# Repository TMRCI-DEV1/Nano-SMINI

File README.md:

# Nano-SMINI
Arduino Nano-based CMRI SMINI

Shield: [![CC BY-SA 4.0][cc-by-sa-shield]][cc-by-sa]

This work is licensed under a
[Creative Commons Attribution-ShareAlike 4.0 International License][cc-by-sa].

[![CC BY-SA 4.0][cc-by-sa-image]][cc-by-sa]

[cc-by-sa]: http://creativecommons.org/licenses/by-sa/4.0/
[cc-by-sa-image]: https://licensebuttons.net/l/by-sa/4.0/88x31.png
[cc-by-sa-shield]: https://img.shields.io/badge/License-CC%20BY--SA%204.0-lightgrey.svg

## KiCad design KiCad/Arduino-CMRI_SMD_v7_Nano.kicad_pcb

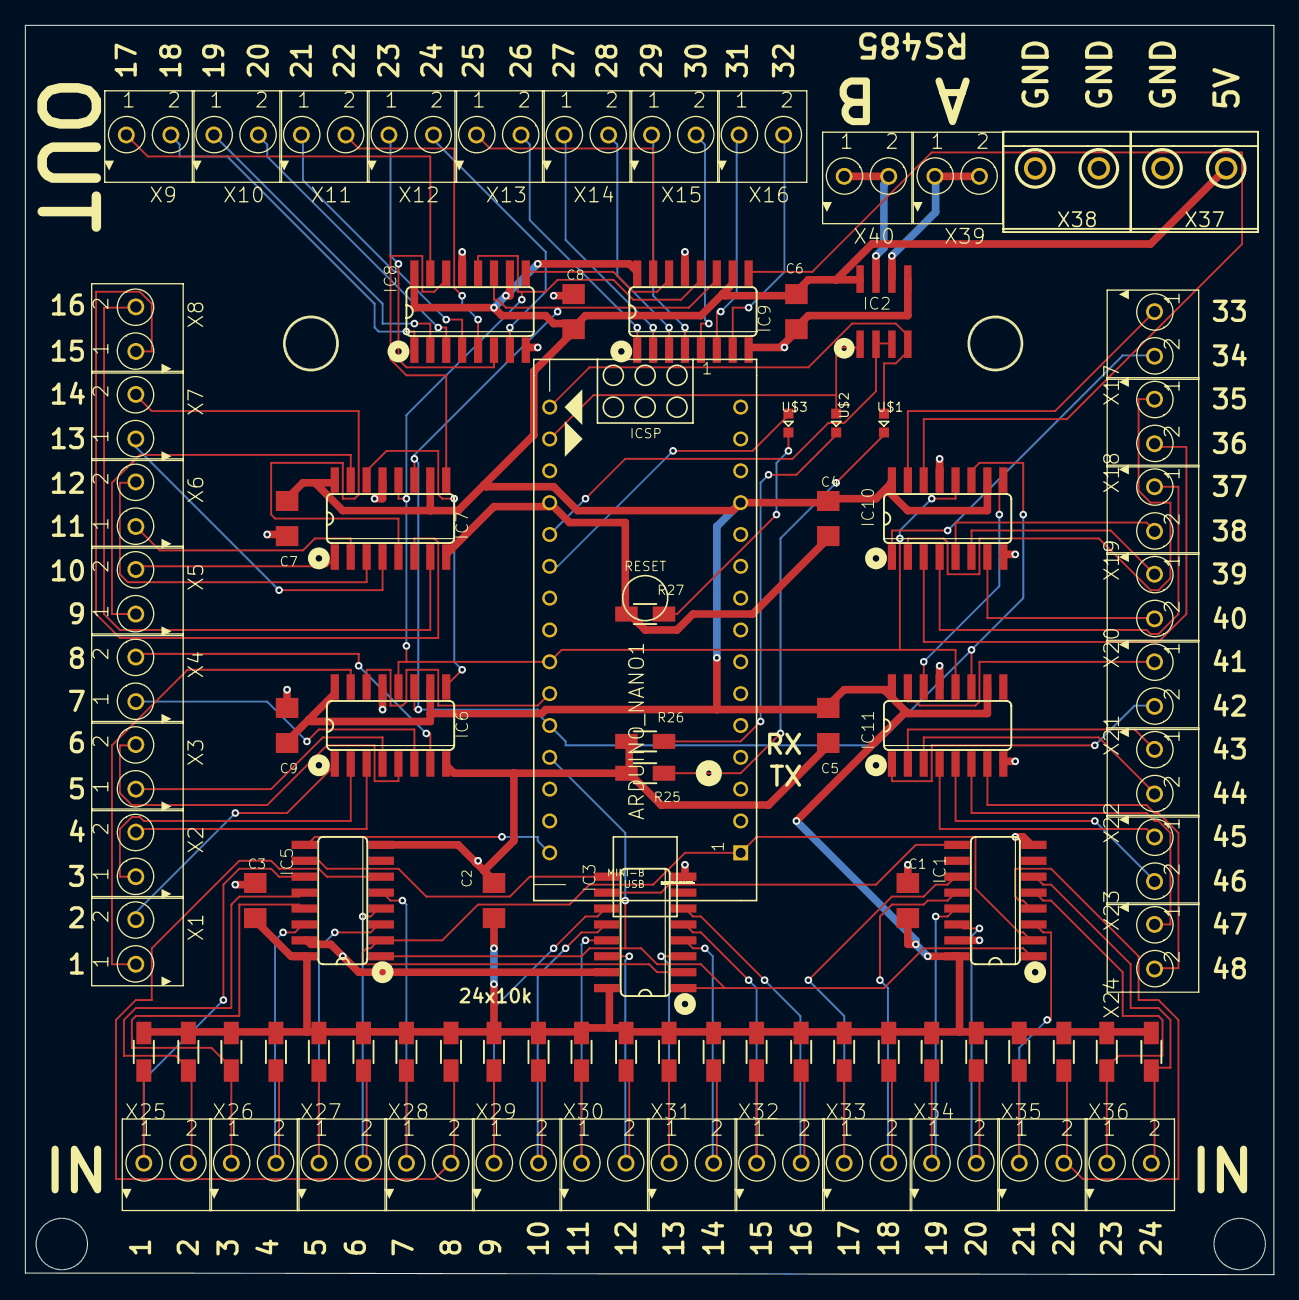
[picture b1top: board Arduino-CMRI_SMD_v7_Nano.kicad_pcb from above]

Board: 2 copper layers, 99.6 x 99.7 mm, 92 parts (0 on the bottom side), 96 nets.

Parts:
ARDUINO_NANO1: ARDUINO_NANO
C1, C2, C3, C4, C5, C6, C7, C8, C9: 100nF; 1206
H1, H2: MOUNT-HOLE4.1; 4,1
IC1, IC3, IC5: 74HC165D; SO16
IC2: MAX485; SO08
IC6, IC7, IC8, IC9, IC10, IC11: 74HC595D; SO16
R1, R2, R3, R4, R5, R6, R7, R8, R9, R10, R11, R12, R13, R14, R15, R16, R17, R18, R19, R20, R21, R22, R23, R24: 10k; R1206W
R25, R26, R27: 1k; R1206W
U$1: TX; CHIPLED_0603
U$2: RX; CHIPLED_0603
U$3: status; CHIPLED_0603
X1, X2, X3, X4, X5, X6, X7, X8, X9, X10, X11, X12, X13, X14, X15, X16, X17, X18, X19, X20, X21, X22, X23, X24, X25, X26, X27, X28, X29, X30, X31, X32, X33, X34, X35, X36, X39, X40: TERMINAL_2P_3,5MM_V2; TERMINAL_2P_3,5MM
X37, X38: W237-132

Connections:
A: IC2.6, X39.P$1, X39.P$2
B: IC2.7, X40.P$1, X40.P$2
D2: ARDUINO_NANO1.20, IC2.2, IC2.3
D3: ARDUINO_NANO1.21, U$3.A
D6: ARDUINO_NANO1.24, IC6.12, IC7.12, IC8.12, IC9.12, IC10.12, IC11.12
D7: ARDUINO_NANO1.25, IC6.14
D8: ARDUINO_NANO1.26, IC6.11, IC7.11, IC8.11, IC9.11, IC10.11, IC11.11
D9: ARDUINO_NANO1.27, IC1.1, IC3.1, IC5.1
D12: ARDUINO_NANO1.30, IC5.9
D13: ARDUINO_NANO1.1, IC1.2, IC3.2, IC5.2
GND: ARDUINO_NANO1.14, ARDUINO_NANO1.19, C1.1, C2.1, C3.1, C4.1, C5.1, C6.1, C7.1, C8.1, C9.1, IC1.8, IC1.15, IC2.5, IC3.8, IC3.15, IC5.8, IC5.15, IC6.8, IC6.13, IC7.8, IC7.13, IC8.8, IC8.13, IC9.8, IC9.13, IC10.8, IC10.13, IC11.8, IC11.13, R25.1, R26.1, R27.1, X37.2, X38.1, X38.2
unnamed: IC5.11, R24.1, X25.P$1
unnamed: IC1.9, IC3.10
unnamed: IC5.12, R23.1, X25.P$2
unnamed: IC3.9, IC5.10
unnamed: IC5.13, R22.1, X26.P$1
unnamed: IC6.9, IC7.14
unnamed: IC5.14, R21.1, X26.P$2
unnamed: IC9.9, IC10.14
unnamed: IC5.3, R20.1, X27.P$1
unnamed: IC7.9, IC8.14
unnamed: IC5.4, R19.1, X27.P$2
unnamed: IC10.9, IC11.14
unnamed: IC5.5, R18.1, X28.P$1
unnamed: IC6.15, X1.P$1
unnamed: IC5.6, R17.1, X28.P$2
unnamed: IC6.1, X1.P$2
unnamed: R25.2, U$1.C
unnamed: IC6.2, X2.P$1
unnamed: IC3.11, R16.1, X29.P$1
unnamed: IC6.3, X2.P$2
unnamed: IC3.12, R15.1, X29.P$2
unnamed: IC6.4, X3.P$1
unnamed: IC3.13, R14.1, X30.P$1
unnamed: IC6.5, X3.P$2
unnamed: IC3.14, R13.1, X30.P$2
unnamed: IC6.6, X4.P$1
unnamed: IC3.3, R12.1, X31.P$1
unnamed: IC6.7, X4.P$2
unnamed: IC3.4, R11.1, X31.P$2
unnamed: IC7.15, X5.P$1
unnamed: IC3.5, R10.1, X32.P$1
unnamed: IC7.1, X5.P$2
unnamed: IC3.6, R9.1, X32.P$2
unnamed: IC7.2, X6.P$1
unnamed: IC1.11, R8.1, X33.P$1
unnamed: IC7.3, X6.P$2
unnamed: IC1.12, R7.1, X33.P$2
unnamed: IC7.4, X7.P$1
unnamed: IC1.13, R6.1, X34.P$1
unnamed: IC7.5, X7.P$2
unnamed: IC1.14, R5.1, X34.P$2
unnamed: IC7.6, X8.P$1
unnamed: IC1.3, R4.1, X35.P$1
unnamed: IC7.7, X8.P$2
unnamed: IC1.4, R3.1, X35.P$2
unnamed: IC8.15, X9.P$1
unnamed: IC1.5, R2.1, X36.P$1
unnamed: IC8.1, X9.P$2
unnamed: IC8.2, X10.P$1
unnamed: IC8.3, X10.P$2
unnamed: IC8.9, IC9.14
unnamed: IC8.4, X11.P$1
unnamed: IC8.5, X11.P$2
unnamed: R26.2, U$2.C
unnamed: IC1.6, R1.1, X36.P$2
unnamed: R27.2, U$3.C
unnamed: IC8.6, X12.P$1
unnamed: IC8.7, X12.P$2
unnamed: IC9.15, X13.P$1
unnamed: IC9.1, X13.P$2
unnamed: IC9.2, X14.P$1
unnamed: IC9.3, X14.P$2
unnamed: IC9.4, X15.P$1
unnamed: IC9.5, X15.P$2
unnamed: IC9.6, X16.P$1
unnamed: IC9.7, X16.P$2
unnamed: IC10.15, X17.P$1
unnamed: IC10.1, X17.P$2
unnamed: IC10.2, X18.P$1
unnamed: IC10.3, X18.P$2
unnamed: IC10.4, X19.P$1
unnamed: IC10.5, X19.P$2
unnamed: IC10.6, X20.P$1
unnamed: IC10.7, X20.P$2
unnamed: IC11.15, X21.P$1
unnamed: IC11.1, X21.P$2
unnamed: IC11.2, X22.P$1
unnamed: IC11.3, X22.P$2
unnamed: IC11.4, X23.P$1
unnamed: IC11.5, X23.P$2
unnamed: IC11.6, X24.P$1
unnamed: IC11.7, X24.P$2
RX: ARDUINO_NANO1.17, IC2.1, U$2.A
TX: ARDUINO_NANO1.16, IC2.4, U$1.A
VCC: ARDUINO_NANO1.12, C1.2, C2.2, C3.2, C4.2, C5.2, C6.2, C7.2, C8.2, C9.2, IC1.16, IC2.8, IC3.16, IC5.16, IC6.10, IC6.16, IC7.10, IC7.16, IC8.10, IC8.16, IC9.10, IC9.16, IC10.10, IC10.16, IC11.10, IC11.16, R1.2, R2.2, R3.2, R4.2, R5.2, R6.2, R7.2, R8.2, R9.2, R10.2, R11.2, R12.2, R13.2, R14.2, R15.2, R16.2, R17.2, R18.2, R19.2, R20.2, R21.2, R22.2, R23.2, R24.2, X37.1

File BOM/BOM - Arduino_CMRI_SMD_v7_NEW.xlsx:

Designators | Value | Footprint | Manufacturer Part Number | Quantity
C1, C2, C3, C4, C5, C6, C7, C8, C9 | 100nF | 1206 | CL31B104KBCNNNC | 9
R1, R2, R3, R4, R5, R6, R7, R8, R9, R10, R11, R12, R13, R14, R15, R16, R17, R18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 | 10k | 1206 | 1206W4F1002T5E | 24
R25, R26, R27 | 1k | 1206 | 1206W4F1001T5 | 3
X1, X2, X3, X4, X5, X6, X7, X8, X9, X10, X11, X12, X13, X14, X15, X16, X17, X18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 | TERMINAL_7.5X7.3MM_TM | TERMINAL_7.5X7.3MM_TM | KF350-3.5-2P | 38
X37, X38 | TERMINAL_10.16X8.1MM_TM | TERMINAL_10.16X8.1MM_TM | WJ128V-5.0-2P | 2
IC6, IC7, IC8, IC9, IC10, IC11 | 74HC595D | SOP16_150MIL | 74HC595D | 6
IC1, IC3, IC5 | 74HC165D, 653 | SOIC16_150MIL | 74HC165D,653 | 3
H1, H2 | MOUNT-HOLE4.1 | 4,1 |  | 2 |  | DNP
ARDUINO_NANO1 |  | ARDUINO_NANO_HEADERS | 15Fx1-254mm | 2 |  | DNP | 15Fx1-254mm
IC2 | MAX485 | SOP8 | MAX485ED | 1
U$1 | TX，CHIPLED_0603, blue | 0603 | LTST-C190TBKT | 1
U$2 | RX，CHIPLED_0603, red | 0603 | LTST-C190KRKT | 1
U$3 | status，CHIPLED_0603, yellow | 0603 | LTST-C190KSKT | 1

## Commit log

2023-04-12 Added full project
2023-05-17 Update Current_OPT_SMINI_Node.ino
    Latest version
2023-05-17 Update Current_OPT_SMINI_Node.ino
    Added header
2023-05-23 Update LICENSE
